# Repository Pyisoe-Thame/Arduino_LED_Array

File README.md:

# 8x24 LED Array, Atmega328PB

This is my PCB Design practice project. ATmega328PB is the upgraded version of ATmega328P which is no longer recommeded for new design at this time. Instead Atmega328PB is in production of microchip with more or less the same price. The distinct feature of this MCU that I noticed is it has an extra SPI protocol and some expansion on memories.

The circuit 4 74595A shift registers; one for 8 LED rows and the others for the columns.
In the circuit I used all four 595 chips have the same CLK pin connect together and 3 of them are daisy-chained to shift a total of 24 columns, the rest one is used for columns each pin cooperated
by a PNP transistor.

While it may not be able to give HIGH to all the LEDs at once, you can use time division multiplexing to achieve the same visual effect by lighting each led at multiple time slots at high frequency.

## Features

- Arudino compatible Atmega328PB-AU
- DC Jack to 5V AMS1117
- Programming with ICSP
- 74HC595A shift registers
- 24 columns, 8 rows of output LEDs

## Screenshots

.JPG)
<p align="center">Front View</p>

.JPG)
<p align="center">Back View</p>

<p align="center">Preview with Components</p>

## License

[MIT](https://choosealicense.com/licenses/mit/)

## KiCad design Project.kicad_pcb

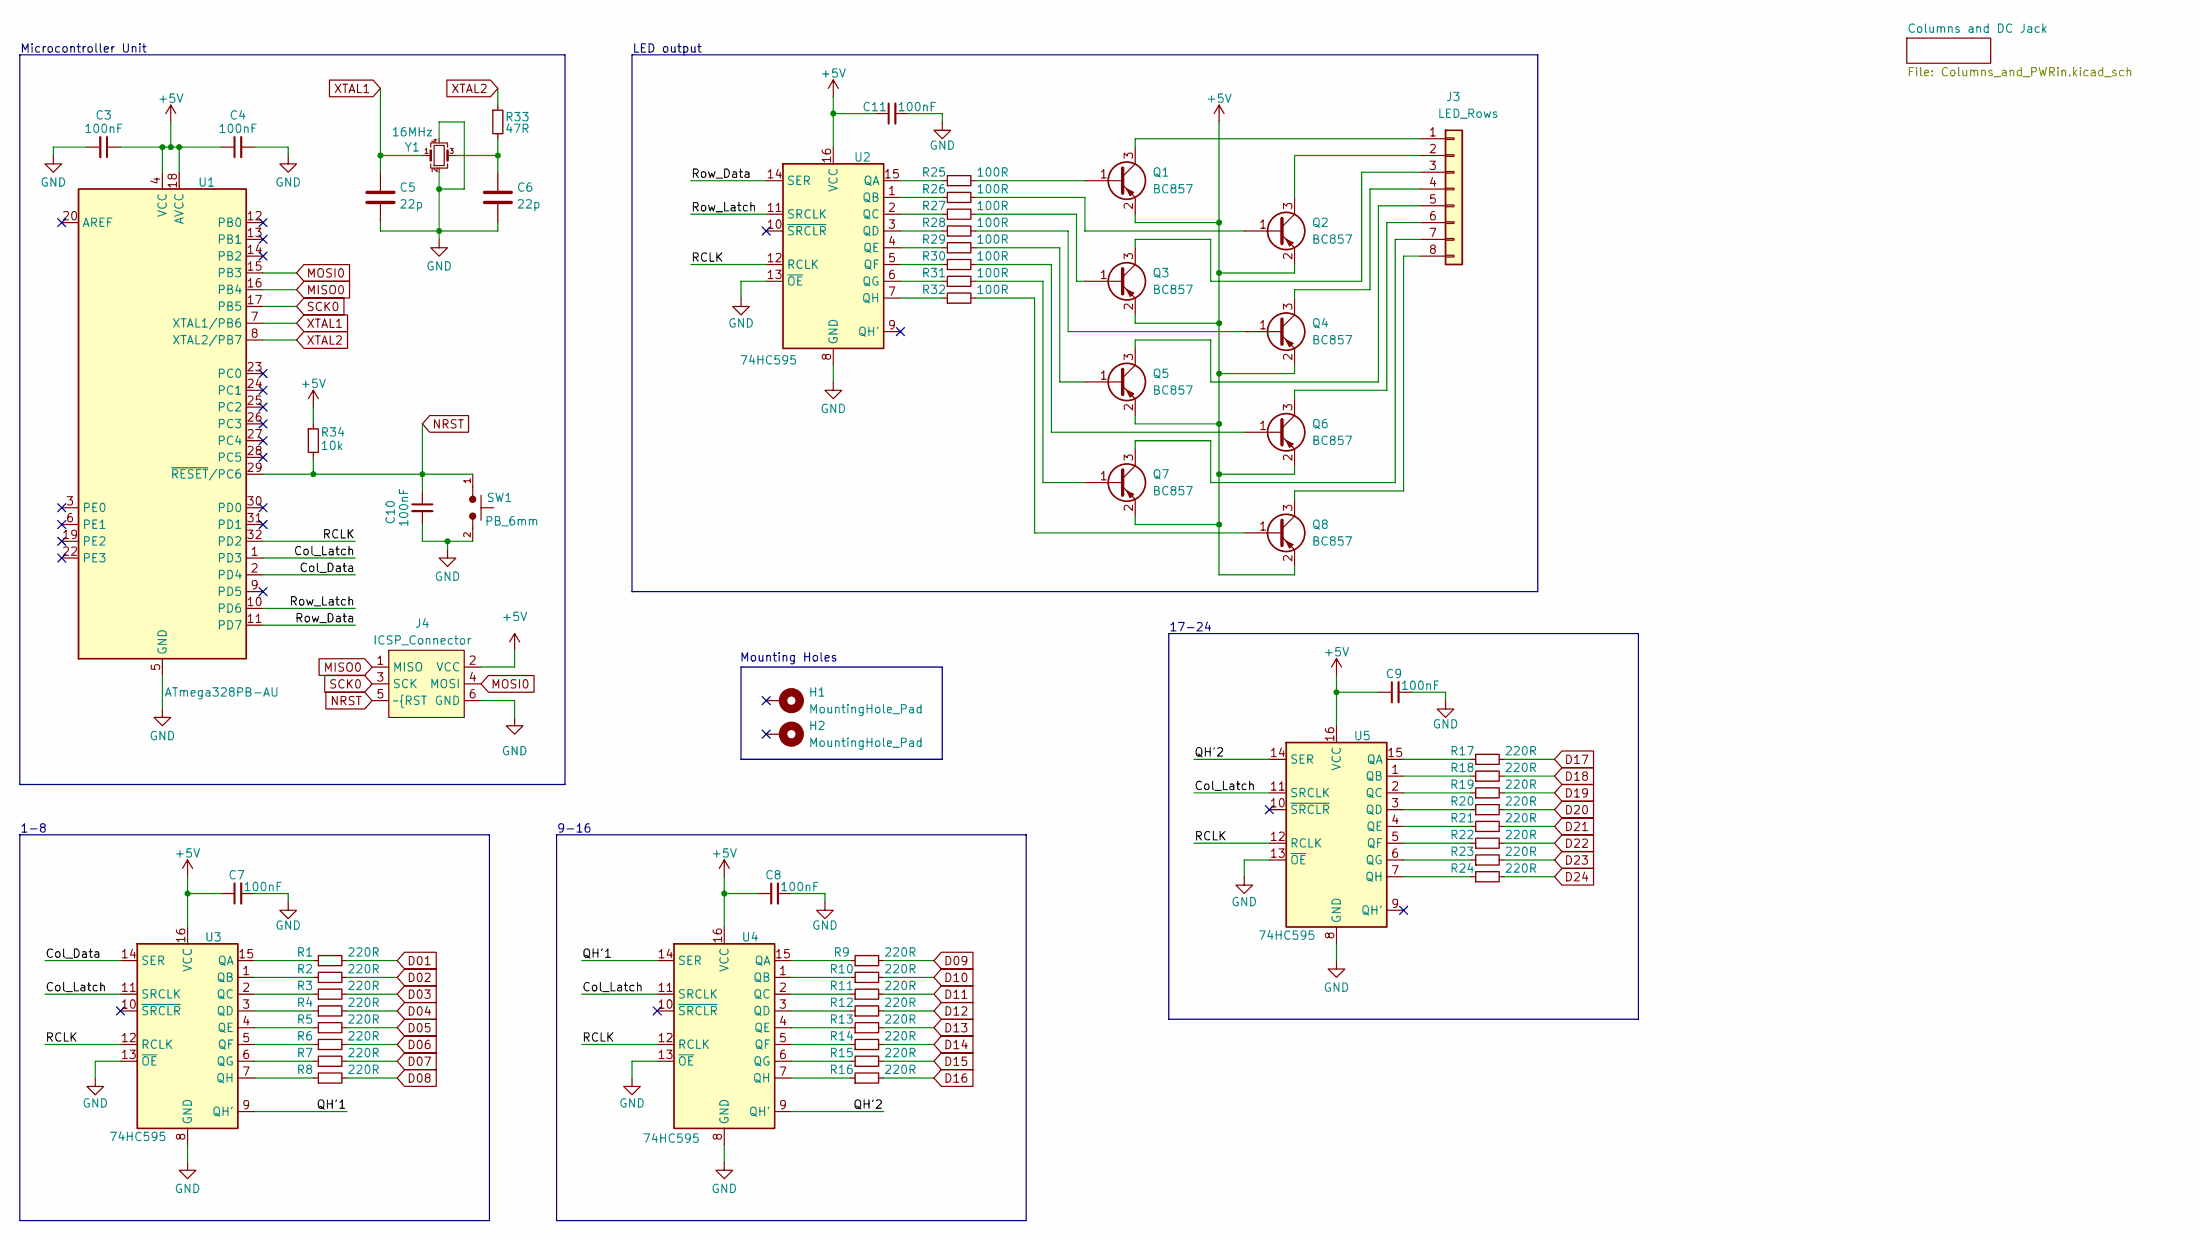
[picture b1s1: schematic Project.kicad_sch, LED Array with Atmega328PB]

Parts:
C3, C4, C7, C8, C9, C10, C11: 100nF; C_0603_1608Metric
C5, C6: 22p; C_0402_1005Metric
H1, H2: MountingHole_Pad; MountingHole_3.2mm_M3_Pad_Via
J3: LED_Rows; PinHeader_1x08_P2.54mm_Vertical
J4: ICSP_Connector; PinHeader_2x03_P2.54mm_Vertical
Q1, Q2, Q3, Q4, Q5, Q6, Q7, Q8: BC857; SOT-23
R1, R2, R3, R4, R5, R6, R7, R8, R9, R10, R11, R12, R13, R14, R15, R16, R17, R18, R19, R20, R21, R22, R23, R24: 220R; R_0603_1608Metric
R25, R26, R27, R28, R29, R30, R31, R32: 100R; R_0603_1608Metric
R33: 47R; R_0603_1608Metric
R34: 10k; R_0603_1608Metric
SW1: PB_6mm; SW_PUSH_6mm
U1: ATmega328PB-AU; TQFP-32_7x7mm_P0.8mm
U2, U3, U4, U5: 74HC595; SOIC-16W_7.5x10.3mm_P1.27mm
Y1: 16MHz; Crystal_SMD_3225-4Pin_3.2x2.5mm

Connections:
+5V: C3.1, C4.1, C7.1, C8.1, C9.1, C11.1, J4.2 (VCC), Q1.2 (E), Q2.2 (E), Q3.2 (E), Q4.2 (E), Q5.2 (E), Q6.2 (E), Q7.2 (E), Q8.2 (E), R34.1, U1.4 (VCC), U1.18 (AVCC), U2.16 (VCC), U3.16 (VCC), U4.16 (VCC), U5.16 (VCC); also elsewhere on the board
/Col_Data: U1.2 (PD4), U3.14 (SER)
/Col_Latch: U1.1 (PD3), U3.11 (SRCLK), U4.11 (SRCLK), U5.11 (SRCLK)
/QH'1: U3.9 (QH'), U4.14 (SER)
/QH'2: U4.9 (QH'), U5.14 (SER)
/RCLK: U1.32 (PD2), U2.12 (RCLK), U3.12 (RCLK), U4.12 (RCLK), U5.12 (RCLK)
/Row_Data: U1.11 (PD7), U2.14 (SER)
/Row_Latch: U1.10 (PD6), U2.11 (SRCLK)
D01: R1.2; also elsewhere on the board
D02: R2.2; also elsewhere on the board
D03: R3.2; also elsewhere on the board
D04: R4.2; also elsewhere on the board
D05: R5.2; also elsewhere on the board
D06: R6.2; also elsewhere on the board
D07: R7.2; also elsewhere on the board
D08: R8.2; also elsewhere on the board
D09: R9.2; also elsewhere on the board
D10: R10.2; also elsewhere on the board
D11: R11.2; also elsewhere on the board
D12: R12.2; also elsewhere on the board
D13: R13.2; also elsewhere on the board
D14: R14.2; also elsewhere on the board
D15: R15.2; also elsewhere on the board
D16: R16.2; also elsewhere on the board
D17: R17.2; also elsewhere on the board
D18: R18.2; also elsewhere on the board
D19: R19.2; also elsewhere on the board
D20: R20.2; also elsewhere on the board
D21: R21.2; also elsewhere on the board
D22: R22.2; also elsewhere on the board
D23: R23.2; also elsewhere on the board
D24: R24.2; also elsewhere on the board
GND: C3.2, C4.2, C5.2, C6.2, C7.2, C8.2, C9.2, C10.2, C11.2, J4.6 (GND), SW1.2, U1.5 (GND), U1.21 (GND), U2.8 (GND), U2.13 (~OE), U3.8 (GND), U3.13 (~OE), U4.8 (GND), U4.13 (~OE), U5.8 (GND), U5.13 (~OE), Y1.2, Y1.4; also elsewhere on the board
MISO0: J4.1 (MISO), U1.16 (PB4)
MOSI0: J4.4 (MOSI), U1.15 (PB3)
NRST: C10.1, J4.5 (~{RST), R34.2, SW1.1, U1.29 (~RESET/PC6)
unnamed: C6.1, R33.2, Y1.3
unnamed: J3.1, Q1.3 (C)
unnamed: J3.2, Q2.3 (C)
unnamed: J3.3, Q3.3 (C)
unnamed: J3.4, Q4.3 (C)
unnamed: J3.5, Q5.3 (C)
unnamed: J3.6, Q6.3 (C)
unnamed: J3.7, Q7.3 (C)
unnamed: J3.8, Q8.3 (C)
unnamed: Q1.1 (B), R25.2
unnamed: Q2.1 (B), R26.2
unnamed: Q3.1 (B), R27.2
unnamed: Q4.1 (B), R28.2
unnamed: Q5.1 (B), R29.2
unnamed: Q6.1 (B), R30.2
unnamed: Q7.1 (B), R31.2
unnamed: Q8.1 (B), R32.2
unnamed: R25.1, U2.15 (QA)
unnamed: R26.1, U2.1 (QB)
unnamed: R27.1, U2.2 (QC)
unnamed: R28.1, U2.3 (QD)
unnamed: R29.1, U2.4 (QE)
unnamed: R30.1, U2.5 (QF)
unnamed: R31.1, U2.6 (QG)
unnamed: R32.1, U2.7 (QH)
unnamed: R1.1, U3.15 (QA)
unnamed: R2.1, U3.1 (QB)
unnamed: R3.1, U3.2 (QC)
unnamed: R4.1, U3.3 (QD)
unnamed: R5.1, U3.4 (QE)
unnamed: R6.1, U3.5 (QF)
unnamed: R7.1, U3.6 (QG)
unnamed: R8.1, U3.7 (QH)
unnamed: R9.1, U4.15 (QA)
unnamed: R10.1, U4.1 (QB)
unnamed: R11.1, U4.2 (QC)
unnamed: R12.1, U4.3 (QD)
unnamed: R13.1, U4.4 (QE)
unnamed: R14.1, U4.5 (QF)
unnamed: R15.1, U4.6 (QG)
unnamed: R16.1, U4.7 (QH)
unnamed: R17.1, U5.15 (QA)
unnamed: R18.1, U5.1 (QB)
unnamed: R19.1, U5.2 (QC)
unnamed: R20.1, U5.3 (QD)
unnamed: R21.1, U5.4 (QE)
unnamed: R22.1, U5.5 (QF)
unnamed: R23.1, U5.6 (QG)
unnamed: R24.1, U5.7 (QH)
SCK0: J4.3 (SCK), U1.17 (PB5)
XTAL1: C5.1, U1.7 (XTAL1/PB6), Y1.1
XTAL2: R33.1, U1.8 (XTAL2/PB7)

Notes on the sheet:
1-8
17-24
Mounting Holes
9-16
Microcontroller Unit
LED output

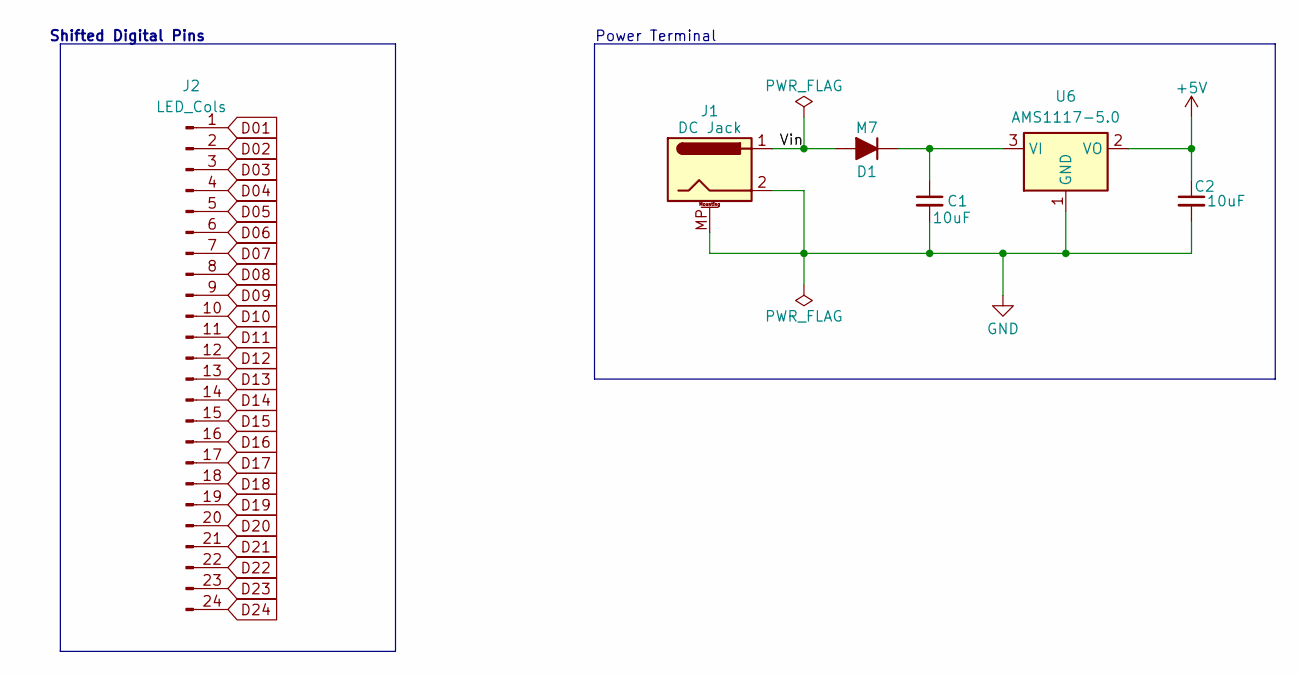
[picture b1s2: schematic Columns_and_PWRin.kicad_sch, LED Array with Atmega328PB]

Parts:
C1, C2: 10uF; C_0805_2012Metric
D1: M7; D_SMB
J1: DC Jack; BarrelJack_Horizontal
J2: LED_Cols; PinHeader_1x24_P2.54mm_Vertical
U6: AMS1117-5.0; SOT-223-3_TabPin2

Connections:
+5V: C2.1, U6.2 (VO); also elsewhere on the board
/Columns and DC Jack/Vin: D1.2 (A), J1.1
D01: J2.1; also elsewhere on the board
D02: J2.2; also elsewhere on the board
D03: J2.3; also elsewhere on the board
D04: J2.4; also elsewhere on the board
D05: J2.5; also elsewhere on the board
D06: J2.6; also elsewhere on the board
D07: J2.7; also elsewhere on the board
D08: J2.8; also elsewhere on the board
D09: J2.9; also elsewhere on the board
D10: J2.10; also elsewhere on the board
D11: J2.11; also elsewhere on the board
D12: J2.12; also elsewhere on the board
D13: J2.13; also elsewhere on the board
D14: J2.14; also elsewhere on the board
D15: J2.15; also elsewhere on the board
D16: J2.16; also elsewhere on the board
D17: J2.17; also elsewhere on the board
D18: J2.18; also elsewhere on the board
D19: J2.19; also elsewhere on the board
D20: J2.20; also elsewhere on the board
D21: J2.21; also elsewhere on the board
D22: J2.22; also elsewhere on the board
D23: J2.23; also elsewhere on the board
D24: J2.24; also elsewhere on the board
GND: C1.2, C2.2, J1.2, J1.MP (MountPin), U6.1 (GND); also elsewhere on the board
unnamed: C1.1, D1.1 (K), U6.3 (VI)

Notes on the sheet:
Power Terminal
Shifted Digital Pins

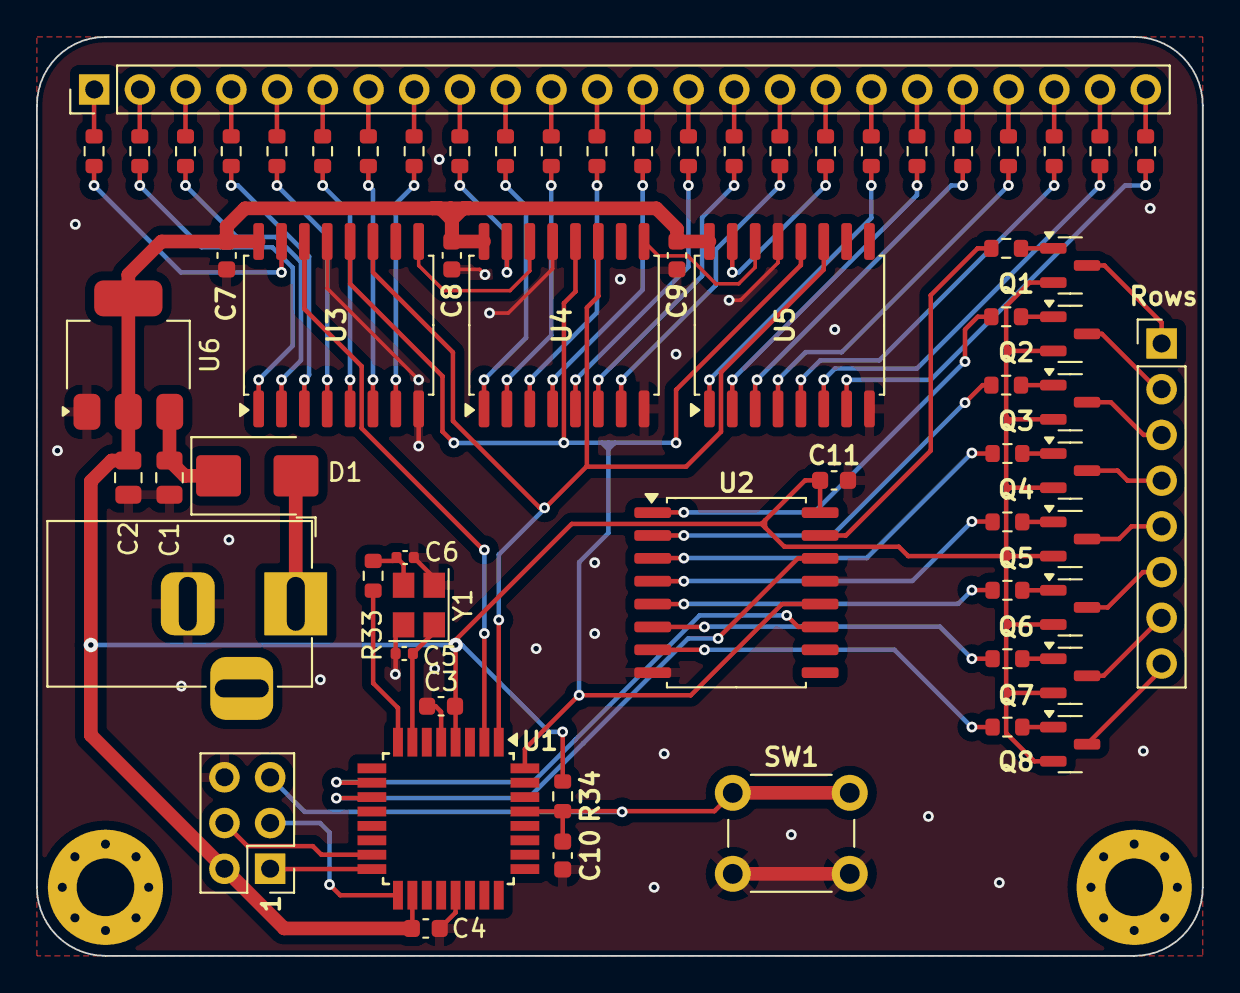
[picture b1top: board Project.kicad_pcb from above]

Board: 2 copper layers, 64.8 x 51.1 mm, 68 parts (0 on the bottom side), 90 nets.

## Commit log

2024-04-16 PCB design done, BOM still undecided
2024-04-26 595 column chip not daisy chained and floating OE pins mistakes corrected
2024-04-26 Rename PCB Preview (F).JPG to PCB Preview.JPG
    Fixing Wrong image name
2024-04-26 Rename PCB Preview (B).JPG to PCB Preview (F).JPG
    Correcting wrong name
2024-04-26 Rename PCB Preview.JPG to PCB Preview (B).JPG
    Change the name
2024-04-26 Update README.md
    fix the images not appearing
